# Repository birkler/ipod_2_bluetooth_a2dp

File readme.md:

# Setup bluetooth a2dp sink

https://scribles.net/streaming-bluetooth-audio-from-phone-to-raspberry-pi-using-alsa/

https://gist.github.com/mill1000/74c7473ee3b4a5b13f6325e9994ff84c
https://gist.github.com/mill1000/74c7473ee3b4a5b13f6325e9994ff84c

sudo unzip -p 2019-04-08-raspbian-stretch-lite.zip | sudo dd of=/dev/sda bs=4M conv=fsync status=progress

# Setup and connect to zero without wifi:

https://raspberrypi.stackexchange.com/questions/73523/connect-pi-zero-via-usb-rndis-gadget-to-ubuntu-17-04

https://github.com/adrianomarto/soft_uart/blob/master/README.md

## Reroute audio to gpio header:

https://raspberrypi.stackexchange.com/questions/49600/how-to-output-audio-signals-through-gpio

https://github.com/raspberrypi/firmware/blob/master/boot/overlays/README

audremap GPIO12-GPIO13

https://raspberrypi.stackexchange.com/questions/83610/gpio-pinout-orientation-raspberypi-zero-w

#ipod interface

https://stackoverflow.com/questions/1720568/whats-needed-to-use-the-apple-accessory-protocol

https://github.com/oandrew/ipod-gadget

http://pinouts.ru/PortableDevices/ipod_pinout.shtml
https://nuxx.net/wiki/iPod_Dock_Connector

https://www.raspberrypi.org/forums/viewtopic.php?f=63&t=163182

sudo apt-get install git

sudo apt-get install python3-serial
sudo apt-get install bluealsa

sudo cp *.service /lib/systemd/system
sudo cp a2dp-agent /usr/local/bin
sudo cp ipod_emul_daemon.py /usr/local/bin

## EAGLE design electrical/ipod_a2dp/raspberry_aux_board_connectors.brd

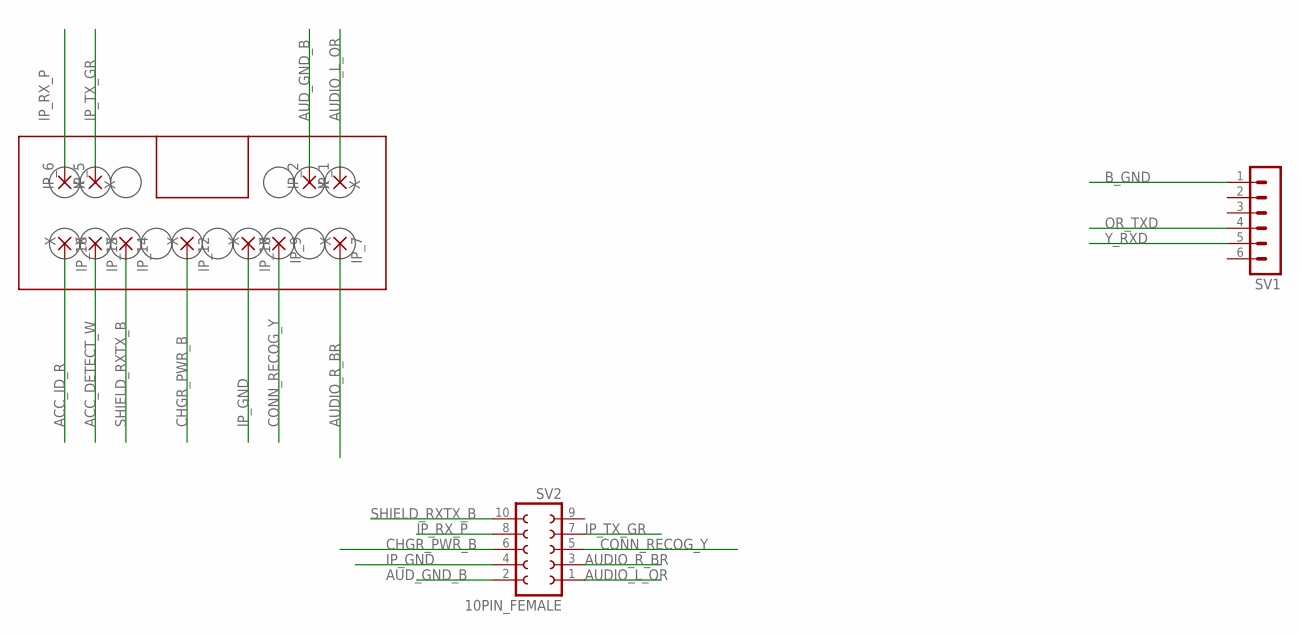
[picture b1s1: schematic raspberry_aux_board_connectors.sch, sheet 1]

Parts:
IP_1, IP_2, IP_5, IP_6, IP_7, IP_9, IP_10, IP_12, IP_14, IP_15, IP_16: X; 2,15/1,0
SV1: MA06-1
SV2: 10PIN_FEMALE; FE05-2

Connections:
ACC_DETECT_W: IP_15.1
ACC_ID_R: IP_16.1
AUDIO_L_OR: IP_1.1, SV2.1
AUDIO_R_BR: IP_7.1, SV2.3
AUD_GND_B: IP_2.1, SV2.2
B_GND: SV1.1
CHGR_PWR_B: IP_12.1, SV2.6
CONN_RECOG_Y: IP_9.1, SV2.5
IP_GND: IP_10.1, SV2.4
IP_RX_P: IP_6.1, SV2.8
IP_TX_GR: IP_5.1, SV2.7
OR_TXD: SV1.4
SHIELD_RXTX_B: IP_14.1, SV2.10
Y_RXD: SV1.5

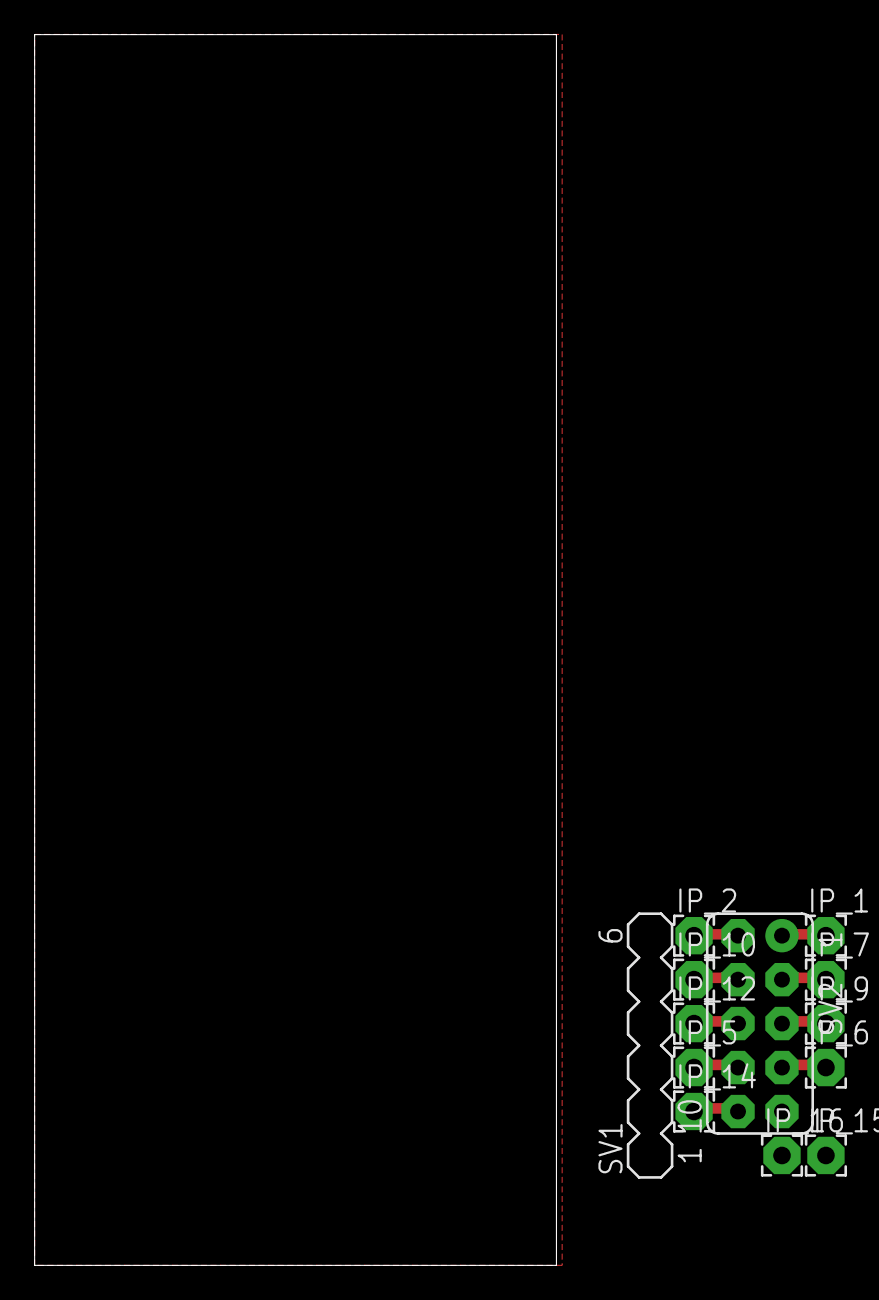
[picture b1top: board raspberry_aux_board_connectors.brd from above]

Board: 2 copper layers, 30.1 x 71.1 mm, 13 parts (0 on the bottom side), 9 nets.

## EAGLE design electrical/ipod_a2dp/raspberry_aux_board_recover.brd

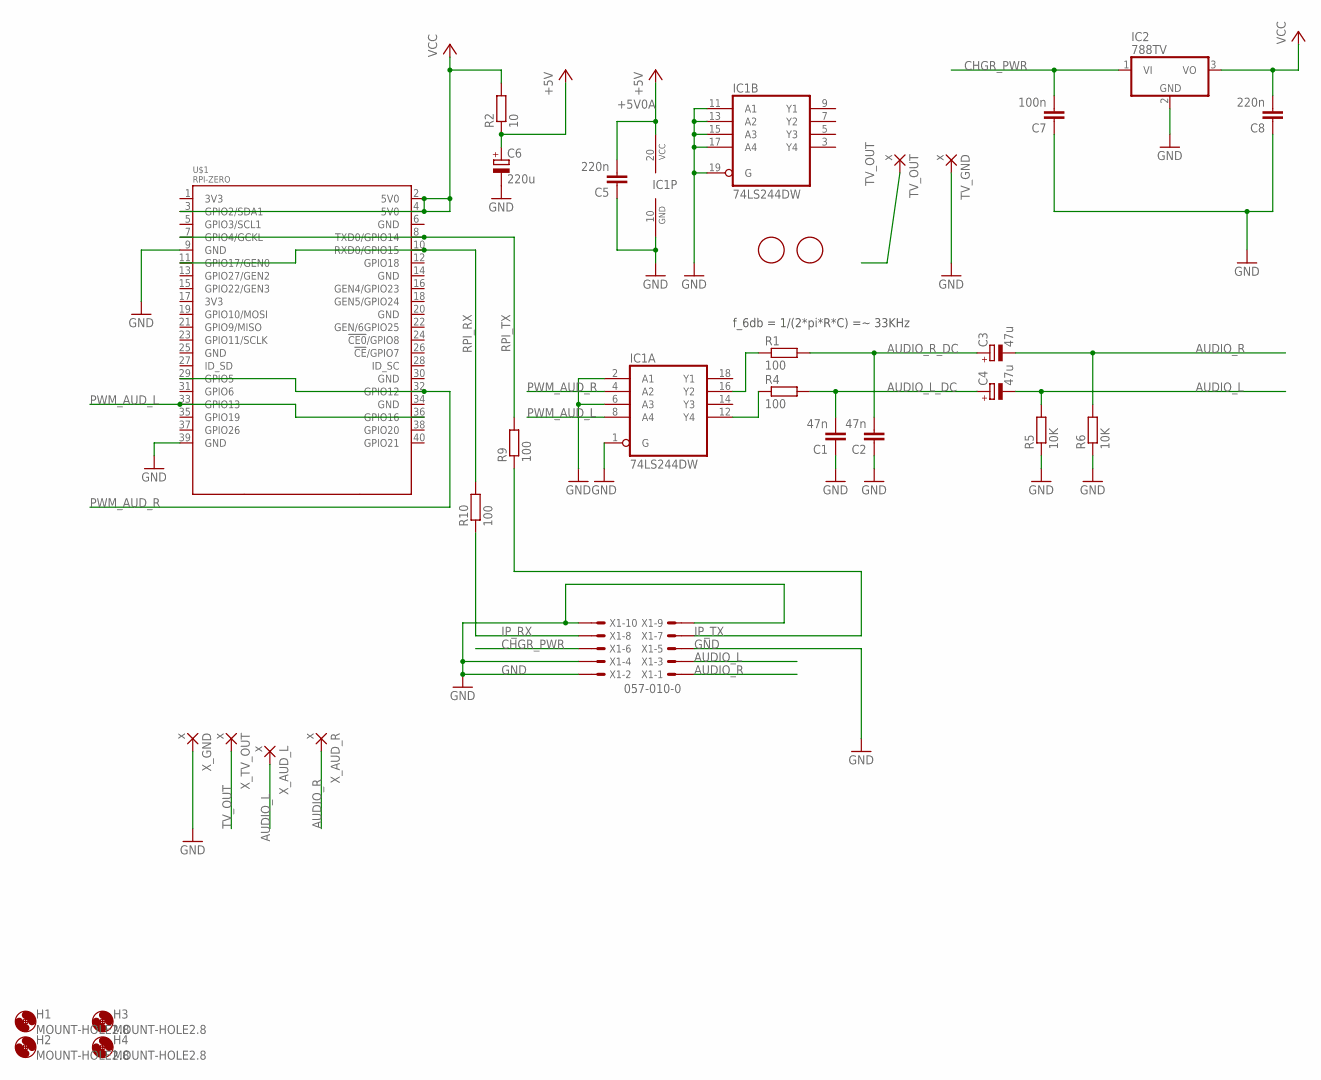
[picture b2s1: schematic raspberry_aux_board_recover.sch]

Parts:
C1, C2: 47n; C050-025X075
C3, C4: 47u; E2,5-5
C5, C8: 220n; C050-050X075
C6: 220u; E5-10,5
C7: 100n; C050-050X075
H1, H2, H3, H4: MOUNT-HOLE2.8; 2,8
IC1: 74LS244DW; SO20W
IC2: 788TV; TO220V
R1, R10: 100; 0207/10
R2: 10; 0204/7
R4, R9: 100; 0204/7
R5, R6: 10K; 0204/5
TV_GND: x; 2,15/1,0
TV_OUT: x; 2,15/1,0
U$1: RPI-ZERO; RASPBERRYPI_BASTELSTUBE_V13_RASPI_BOARD_B+_FULL
U$2, U$3: FIDUCIAL; FIDUCIAL_1MM
X1: 057-010-0
X_AUD_L: x; 2,15/1,0
X_AUD_R: x; 2,15/1,0
X_GND: x; 2,15/1,0
X_TV_OUT: x; 2,15/1,0

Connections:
+5V0A: C5.2, C6.+, IC1.20 (VCC), R2.1
AUDIO_L: C4.-, R5.2, X1.3, X_AUD_L.1
AUDIO_L_DC: C1.2, C4.+, R4.2
AUDIO_R: C3.-, R6.2, X1.1, X_AUD_R.1
AUDIO_R_DC: C2.2, C3.+, R1.2
CHGR_PWR: C7.2, IC2.1 (VI), X1.6
GND: C1.1, C2.1, C5.1, C6.-, C7.1, C8.1, IC1.1 (G), IC1.2 (A1), IC1.6 (A3), IC1.10 (GND), IC1.11 (A1), IC1.13 (A2), IC1.15 (A3), IC1.17 (A4), IC1.19 (G), IC2.2 (GND), R5.1, R6.1, TV_GND.1, U$1.9 (GND), U$1.39 (GND), X1.2, X1.4, X1.5, X1.9, X1.10, X_GND.1
IP_RX: R10.1, X1.8
IP_TX: R9.1, X1.7
unnamed: IC1.12 (Y4), R4.1
unnamed: IC1.16 (Y2), R1.1
PWM_AUD_L: IC1.8 (A4), U$1.33 (GPIO13), U$1.36 (GPIO16)
PWM_AUD_R: IC1.4 (A2), U$1.29 (GPIO5), U$1.32 (GPIO12)
RPI_RX: R10.2, U$1.10 (RXD0/GPIO15), U$1.11 (GPIO17/GEN0)
RPI_TX: R9.2, U$1.7 (GPIO4/GCKL), U$1.8 (TXD0/GPIO14)
TV_OUT: TV_OUT.1, X_TV_OUT.1
VCC: C8.2, IC2.3 (VO), R2.2, U$1.2 (5V0), U$1.3 (GPIO2/SDA1), U$1.4 (5V0)

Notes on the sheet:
f_6db = 1/(2*pi*R*C) =~ 33KHz

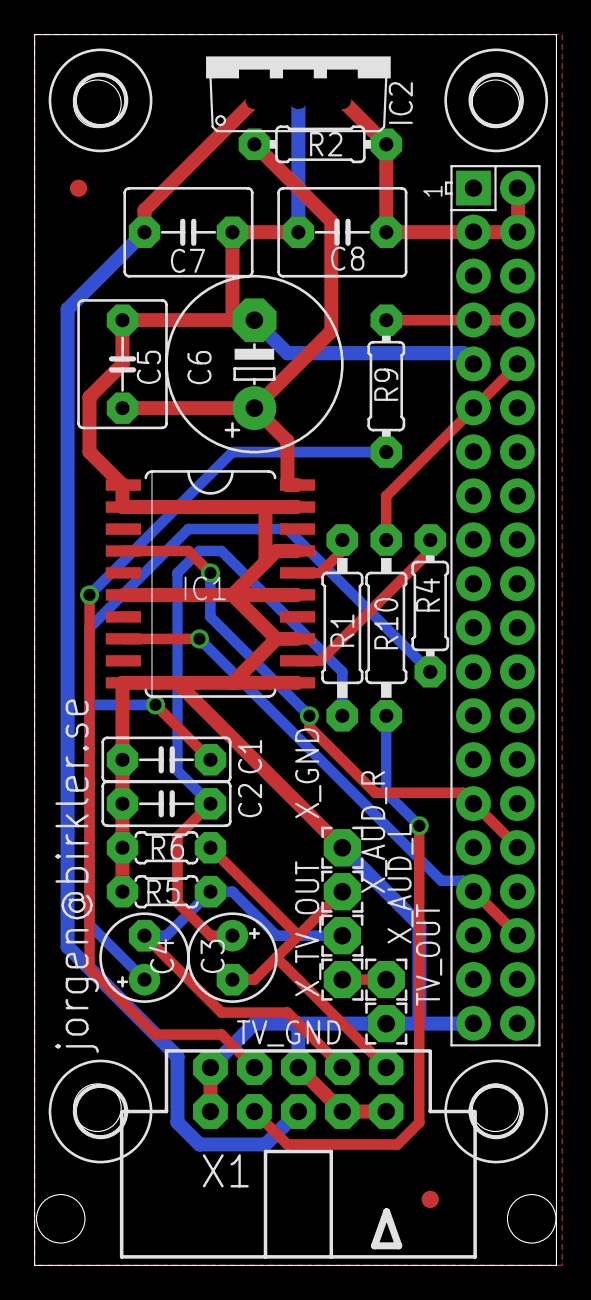
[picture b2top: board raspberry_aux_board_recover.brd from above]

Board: 2 copper layers, 30.1 x 71.1 mm, 31 parts (0 on the bottom side), 17 nets.

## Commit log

2019-04-16 initial files.
2019-04-19 more changes. proto tested. working for audio.
2019-04-23 Emulator somewhat working.
2019-04-23 updated board
2019-04-23 update board and schematic. update daemon for ipod emul
2019-04-30 updated schematic and board. sent to production
2019-04-30 New CAM production with soldermask plus fixes to silkmask
2020-12-11 update codez.
2020-12-29 update install scripts
2020-12-29 update agent services
2020-12-29 fix mv to cp
2020-12-30 fix serial port
2020-12-30 fix serial
